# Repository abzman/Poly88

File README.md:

# Poly88
information related to the Poly88 s100 computer I've been repairing

This repository contains information other than boards, for those I've got a more generic set of S100 repro PCBs that for now mostly contains poly88 stuff: https://github.com/abzman/s100-PCBs

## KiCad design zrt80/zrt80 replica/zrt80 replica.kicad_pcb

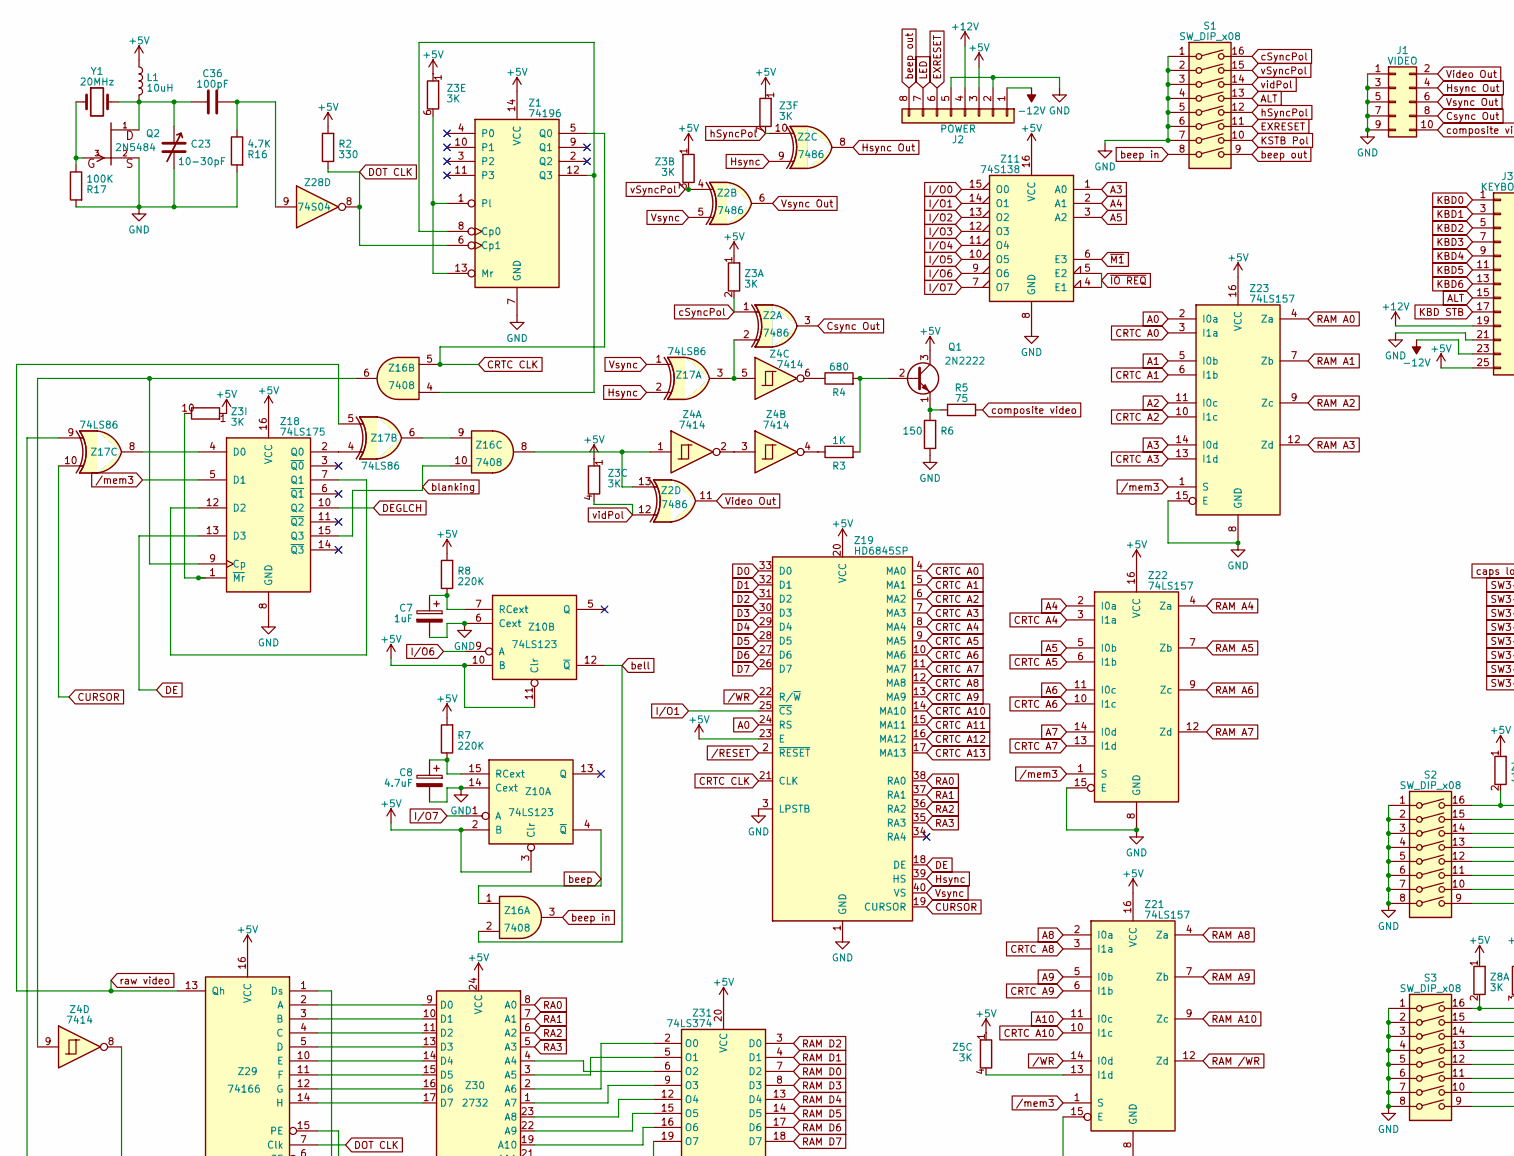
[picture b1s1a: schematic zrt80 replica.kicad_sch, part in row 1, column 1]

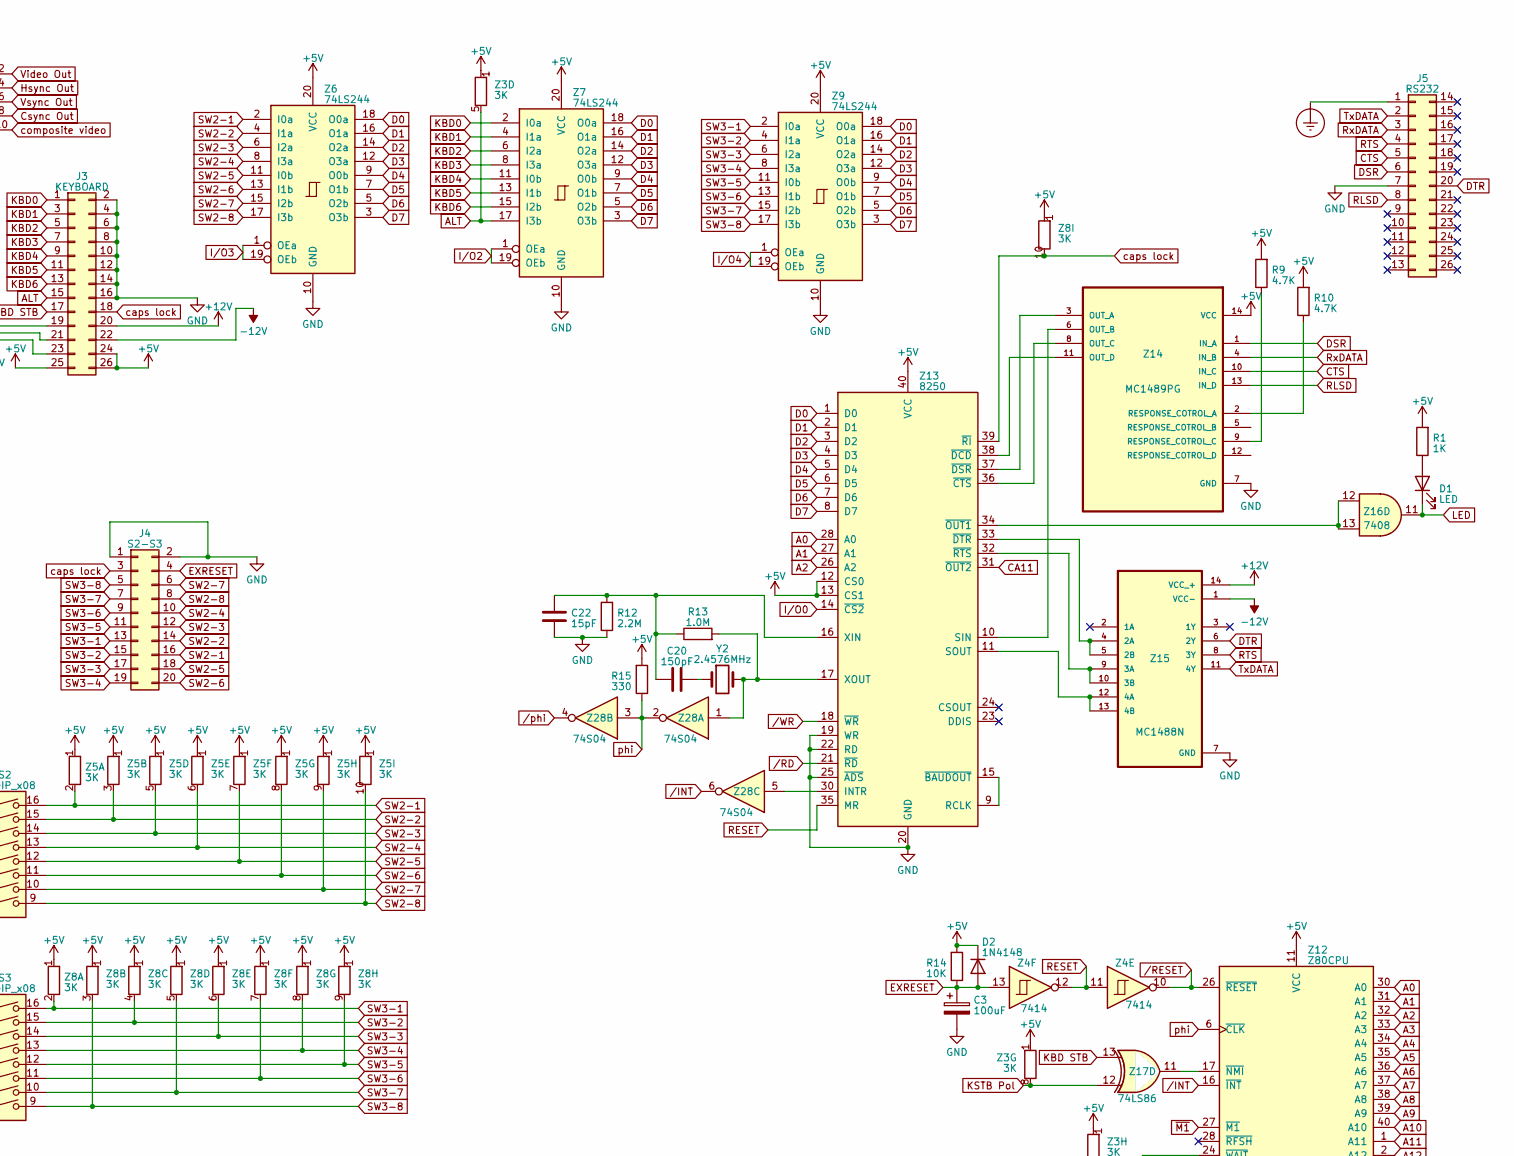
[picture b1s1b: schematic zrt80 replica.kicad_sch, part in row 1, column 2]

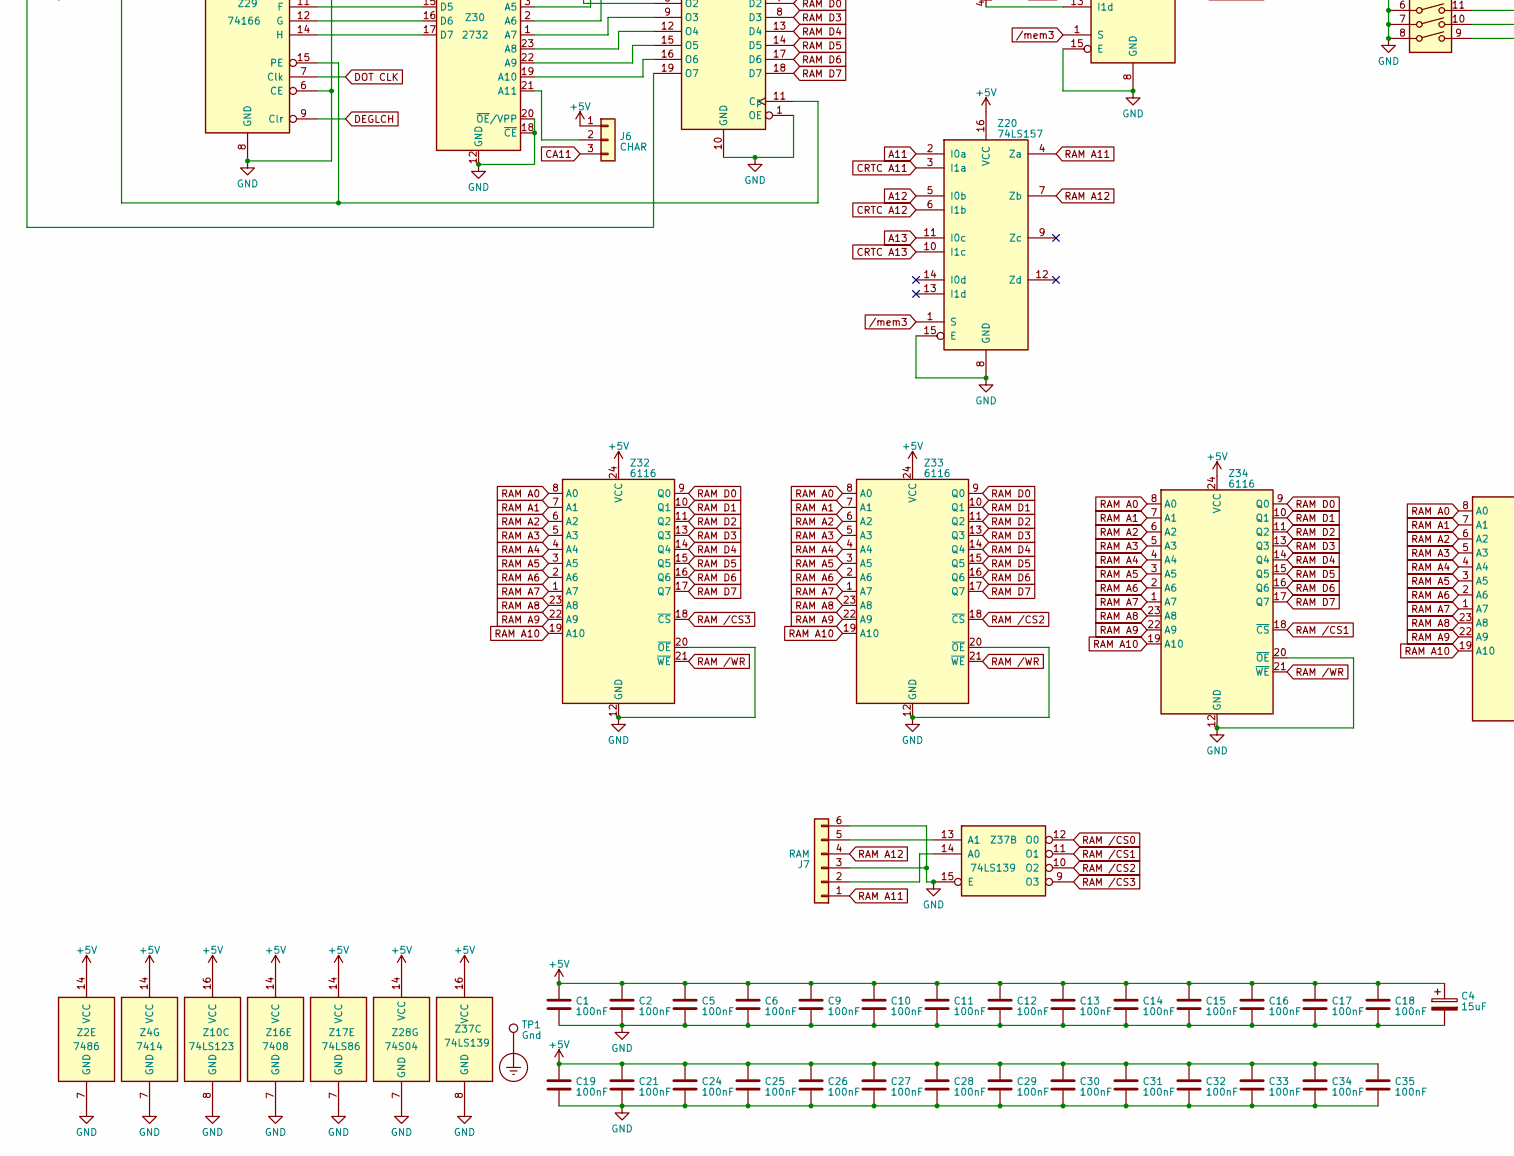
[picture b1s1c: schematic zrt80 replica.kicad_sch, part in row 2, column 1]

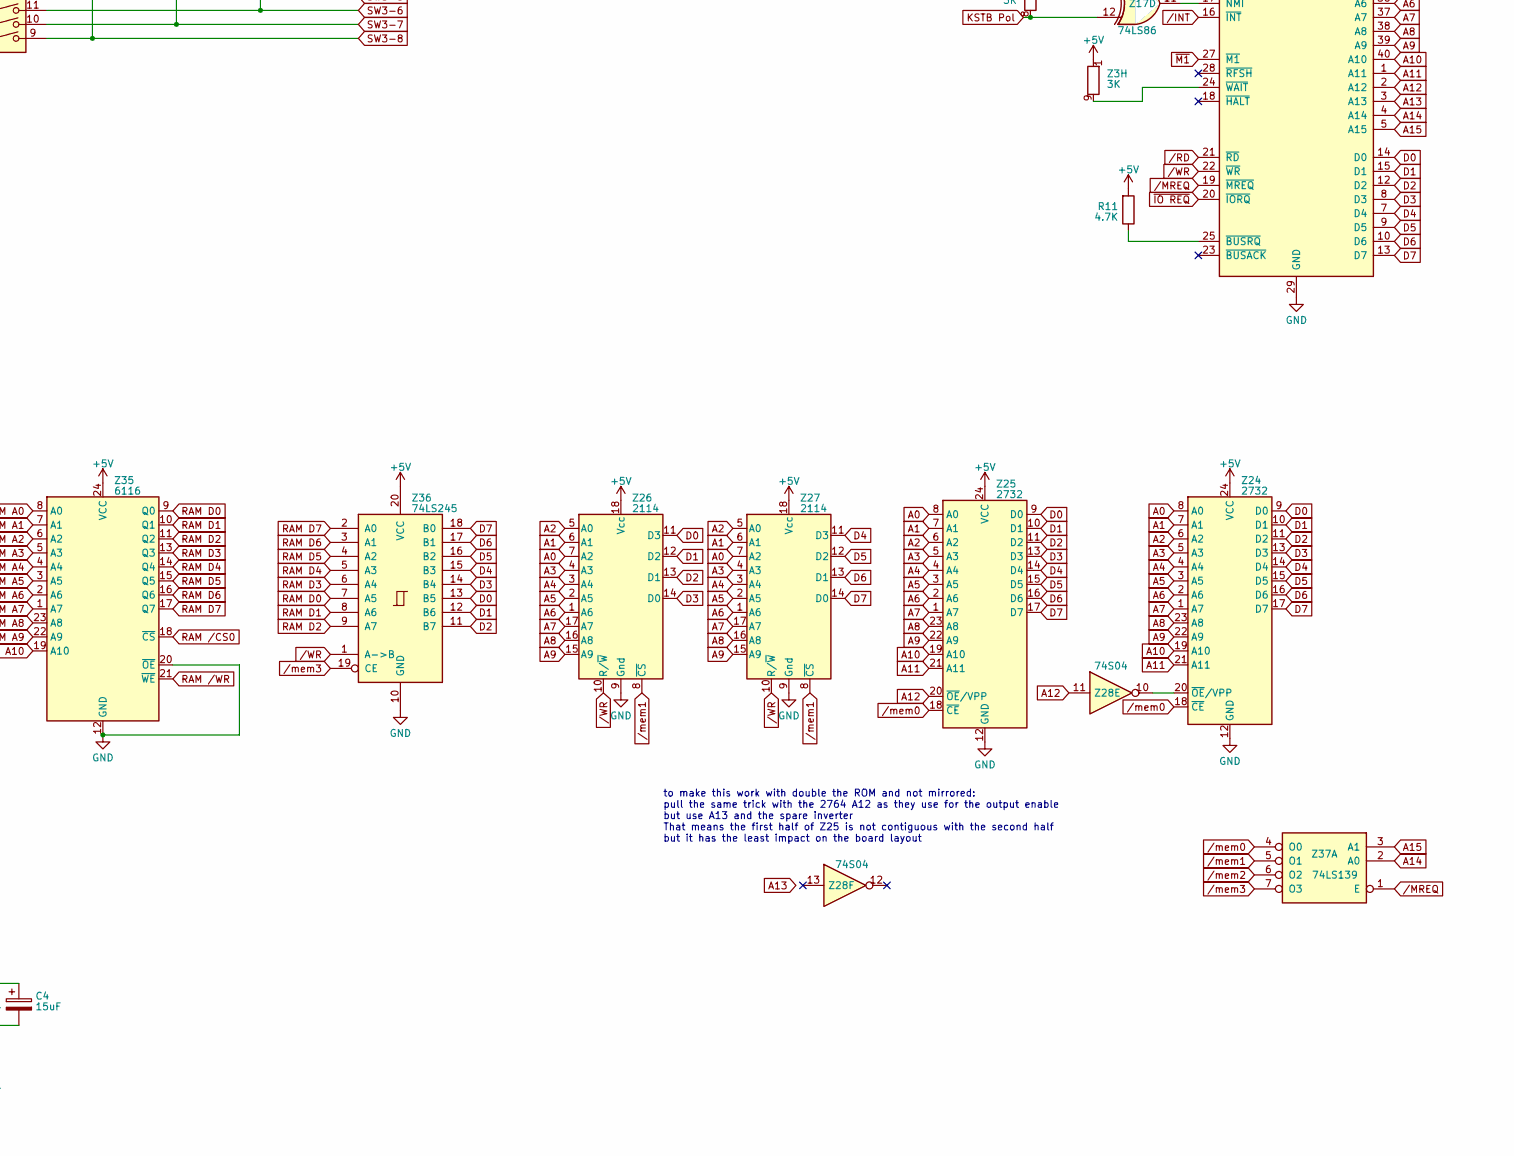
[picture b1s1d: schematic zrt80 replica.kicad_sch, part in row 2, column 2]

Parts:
C1, C2, C5, C6, C9, C10, C11, C12, C13, C14, C15, C16, C17, C18, C19, C21, C24, C25, C26, C27, C28, C29, C30, C31, C32, C33, C34, C35: 100nF; C_Disc_D6.0mm_W2.5mm_P6.35mm
C3: 100uF; CP_Radial_D10.0mm_P5.00mm
C4: 15uF; C_Disc_D6.0mm_W2.5mm_P6.35mm
C7: 1uF; C_Disc_D4.3mm_W1.9mm_P5.00mm
C8: 4.7uF; C_Disc_D4.3mm_W1.9mm_P5.00mm
C20: 150pF; C_Disc_D6.0mm_W2.5mm_P6.35mm
C22: 15pF; C_Disc_D6.0mm_W2.5mm_P6.35mm
C23: 10-30pF; trimmer cap
C36: 100pF; C_Disc_D6.0mm_W2.5mm_P6.35mm
D1: LED; LED_D5.0mm
D2: 1N4148; D_DO-35_SOD27_P12.70mm_Horizontal
J1: VIDEO; PinHeader_2x05_P2.54mm_Vertical
J2: POWER; TerminalBlock_Phoenix_MKDS-1,5-8-5.08_1x08_P5.08mm_Horizont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
J3: KEYBOARD; PinHeader_2x13_P2.54mm_Vertical
J4: S2-S3; PinHeader_2x10_P2.54mm_Vertical
J5: RS232; PinHeader_2x13_P2.54mm_Vertical
J6: CHAR; PinHeader_1x03_P2.54mm_Vertical
J7: RAM; PinHeader_1x06_P2.54mm_Vertical
L1: 10uH; L_Axial_L9.5mm_D4.0mm_P15.24mm_Horizontal_Fastron_SMCC
Q1: 2N2222; TO-5-3
Q2: 2N5484; TO-92L_Inline_Wide; PARTREV December, 2018
R1, R3: 1K; R_Axial_DIN0204_L3.6mm_D1.6mm_P12.7mm_Horizontal
R2, R15: 330; R_Axial_DIN0204_L3.6mm_D1.6mm_P12.7mm_Horizontal
R4: 680; R_Axial_DIN0204_L3.6mm_D1.6mm_P12.7mm_Horizontal
R5: 75; R_Axial_DIN0204_L3.6mm_D1.6mm_P12.7mm_Horizontal
R6: 150; R_Axial_DIN0204_L3.6mm_D1.6mm_P12.7mm_Horizontal
R7, R8: 220K; R_Axial_DIN0204_L3.6mm_D1.6mm_P12.7mm_Horizontal
R9, R10, R11, R16: 4.7K; R_Axial_DIN0204_L3.6mm_D1.6mm_P12.7mm_Horizontal
R12: 2.2M; R_Axial_DIN0204_L3.6mm_D1.6mm_P12.7mm_Horizontal
R13: 1.0M; R_Axial_DIN0204_L3.6mm_D1.6mm_P12.7mm_Horizontal
R14: 10K; R_Axial_DIN0204_L3.6mm_D1.6mm_P12.7mm_Horizontal
R17: 100K; R_Axial_DIN0204_L3.6mm_D1.6mm_P12.7mm_Horizontal
S1, S2, S3: SW_DIP_x08; SW_DIP_SPSTx08_Slide_6.7x21.88mm_W7.62mm_P2.54mm_LowProfile
TP1: Gnd; TestPoint_Plated_Hole_D2.0mm
Y1: 20MHz; Crystal_HC49-U_Vertical
Y2: 2.4576MHz; Crystal_HC33-U_Vertical
Z1: 74196; DIP-14_W7.62mm
Z2: 7486; DIP-14_W7.62mm
Z3, Z5, Z8: 3K; R_Array_SIP10
Z4: 7414; DIP-14_W7.62mm
Z6, Z7, Z9: 74LS244; DIP-20_W7.62mm
Z10: 74LS123; DIP-16_W7.62mm
Z11: 74S138; DIP-16_W7.62mm
Z12: Z80CPU; DIP-40_W15.24mm
Z13: 8250; DIP-40_W15.24mm
Z14: MC1489PG; DIP-14_W7.62mm; MPN MC1489PG
Z15: MC1488N; DIP-14_W7.62mm
Z16: 7408; DIP-14_W7.62mm
Z17: 74LS86; DIP-14_W7.62mm
Z18: 74LS175; DIP-16_W7.62mm
Z19: HD6845SP; DIP-40_W15.24mm
Z20, Z21, Z22, Z23: 74LS157; DIP-16_W7.62mm
Z24, Z25, Z30: 2732; DIP-24_W15.24mm
Z26, Z27: 2114; DIP-18_W7.62mm
Z28: 74S04; DIP-14_W7.62mm
Z29: 74166; DIP-16_W7.62mm
Z31: 74LS374; DIP-20_W7.62mm
Z32, Z33, Z34, Z35: 6116; DIP-24_W15.24mm
Z36: 74LS245; DIP-20_W7.62mm
Z37: 74LS139; DIP-16_W7.62mm

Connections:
+5V: C1.1, C2.1, C4.1, C5.1, C6.1, C9.1, C10.1, C11.1, C12.1, C13.1, C14.1, C15.1, C16.1, C17.1, C18.1, C19.1, C21.1, C24.1, C25.1, C26.1, C27.1, C28.1, C29.1, C30.1, C31.1, C32.1, C33.1, C34.1, C35.1, D2.1 (K), J2.3, J3.24, J3.25, J3.26, J6.1, L1.1, Q1.3 (C), R1.2, R2.2, R7.2, R8.2, R9.2, R10.2, R11.2, R14.2, R15.2, Z1.14 (VCC), Z2.14 (VCC), Z3.1 (R1.1), Z4.14 (VCC), Z5.1 (R1.1), Z6.20 (VCC), Z7.20 (VCC), Z8.1 (R1.1), Z9.20 (VCC), Z10.2 (B), Z10.3 (Clr), Z10.10 (B), Z10.11 (Clr), Z10.16 (VCC), Z11.16 (VCC), Z12.11 (VCC), Z13.12 (CS0), Z13.13 (CS1), Z13.40 (VCC), Z14.14 (VCC), Z16.14 (VCC), Z17.14 (VCC), Z18.16 (VCC), Z19.20 (VCC), Z19.23 (E), Z20.16 (VCC), Z21.16 (VCC), Z22.16 (VCC), Z23.16 (VCC), Z24.24 (VCC), Z25.24 (VCC), Z26.18 (Vcc), Z27.18 (Vcc), Z28.14 (VCC), Z29.16 (VCC), Z30.24 (VCC), Z31.20 (VCC), Z32.24 (VCC), Z33.24 (VCC), Z34.24 (VCC), Z35.24 (VCC), Z36.20 (VCC), Z37.16 (VCC)
+12V: J2.4, J3.19, J3.20, Z15.14 (VCC_+)
-12V: J2.1, J3.22, J3.23, Z15.1 (VCC-)
A0: Z12.30 (A0), Z13.28 (A0), Z19.24 (RS), Z23.2 (I0a), Z24.8 (A0), Z25.8 (A0), Z26.7 (A2), Z27.7 (A2)
A1: Z12.31 (A1), Z13.27 (A1), Z23.5 (I0b), Z24.7 (A1), Z25.7 (A1), Z26.6 (A1), Z27.6 (A1)
A2: Z12.32 (A2), Z13.26 (A2), Z23.11 (I0c), Z24.6 (A2), Z25.6 (A2), Z26.5 (A0), Z27.5 (A0)
A3: Z11.1 (A0), Z12.33 (A3), Z23.14 (I0d), Z24.5 (A3), Z25.5 (A3), Z26.4 (A3), Z27.4 (A3)
A4: Z11.2 (A1), Z12.34 (A4), Z22.2 (I0a), Z24.4 (A4), Z25.4 (A4), Z26.3 (A4), Z27.3 (A4)
A5: Z11.3 (A2), Z12.35 (A5), Z22.5 (I0b), Z24.3 (A5), Z25.3 (A5), Z26.2 (A5), Z27.2 (A5)
A6: Z12.36 (A6), Z22.11 (I0c), Z24.2 (A6), Z25.2 (A6), Z26.1 (A6), Z27.1 (A6)
A7: Z12.37 (A7), Z22.14 (I0d), Z24.1 (A7), Z25.1 (A7), Z26.17 (A7), Z27.17 (A7)
A8: Z12.38 (A8), Z21.2 (I0a), Z24.23 (A8), Z25.23 (A8), Z26.16 (A8), Z27.16 (A8)
A9: Z12.39 (A9), Z21.5 (I0b), Z24.22 (A9), Z25.22 (A9), Z26.15 (A9), Z27.15 (A9)
A10: Z12.40 (A10), Z21.11 (I0c), Z24.19 (A10), Z25.19 (A10)
A11: Z12.1 (A11), Z20.2 (I0a), Z24.21 (A11), Z25.21 (A11)
A12: Z12.2 (A12), Z20.5 (I0b), Z25.20 (~OE/VPP), Z28.11
A13: Z12.3 (A13), Z20.11 (I0c)
A14: Z12.4 (A14), Z37.2 (A0)
A15: Z12.5 (A15), Z37.3 (A1)
ALT: J3.15, S1.13, Z3.5 (R4.2), Z7.17 (I3b)
CA11: J6.3, Z13.31 (~OUT2)
CRTC A0: Z19.4 (MA0), Z23.3 (I1a)
CRTC A1: Z19.5 (MA1), Z23.6 (I1b)
CRTC A2: Z19.6 (MA2), Z23.10 (I1c)
CRTC A3: Z19.7 (MA3), Z23.13 (I1d)
CRTC A4: Z19.8 (MA4), Z22.3 (I1a)
CRTC A5: Z19.9 (MA5), Z22.6 (I1b)
CRTC A6: Z19.10 (MA6), Z22.10 (I1c)
CRTC A7: Z19.11 (MA7), Z22.13 (I1d)
CRTC A8: Z19.12 (MA8), Z21.3 (I1a)
CRTC A9: Z19.13 (MA9), Z21.6 (I1b)
CRTC A10: Z19.14 (MA10), Z21.10 (I1c)
CRTC A11: Z19.15 (MA11), Z20.3 (I1a)
CRTC A12: Z19.16 (MA12), Z20.6 (I1b)
CRTC A13: Z19.17 (MA13), Z20.10 (I1c)
CRTC CLK: Z1.5 (Q0), Z16.5, Z19.21 (CLK)
CTS: J5.5, Z14.10 (IN_C)
CURSOR: Z17.10, Z19.19 (CURSOR)
Csync Out: J1.8, Z2.3
D0: Z6.18 (O0a), Z7.18 (O0a), Z9.18 (O0a), Z12.14 (D0), Z13.1 (D0), Z19.33 (D0), Z24.9 (D0), Z25.9 (D0), Z26.11 (D3), Z36.13 (B5)
D1: Z6.16 (O1a), Z7.16 (O1a), Z9.16 (O1a), Z12.15 (D1), Z13.2 (D1), Z19.32 (D1), Z24.10 (D1), Z25.10 (D1), Z26.12 (D2), Z36.12 (B6)
D2: Z6.14 (O2a), Z7.14 (O2a), Z9.14 (O2a), Z12.12 (D2), Z13.3 (D2), Z19.31 (D2), Z24.11 (D2), Z25.11 (D2), Z26.13 (D1), Z36.11 (B7)
D3: Z6.12 (O3a), Z7.12 (O3a), Z9.12 (O3a), Z12.8 (D3), Z13.4 (D3), Z19.30 (D3), Z24.13 (D3), Z25.13 (D3), Z26.14 (D0), Z36.14 (B4)
D4: Z6.9 (O0b), Z7.9 (O0b), Z9.9 (O0b), Z12.7 (D4), Z13.5 (D4), Z19.29 (D4), Z24.14 (D4), Z25.14 (D4), Z27.11 (D3), Z36.15 (B3)
D5: Z6.7 (O1b), Z7.7 (O1b), Z9.7 (O1b), Z12.9 (D5), Z13.6 (D5), Z19.28 (D5), Z24.15 (D5), Z25.15 (D5), Z27.12 (D2), Z36.16 (B2)
D6: Z6.5 (O2b), Z7.5 (O2b), Z9.5 (O2b), Z12.10 (D6), Z13.7 (D6), Z19.27 (D6), Z24.16 (D6), Z25.16 (D6), Z27.13 (D1), Z36.17 (B1)
D7: Z6.3 (O3b), Z7.3 (O3b), Z9.3 (O3b), Z12.13 (D7), Z13.8 (D7), Z19.26 (D7), Z24.17 (D7), Z25.17 (D7), Z27.14 (D0), Z36.18 (B0)
DE: Z18.13 (D3), Z19.18 (DE)
DEGLCH: Z18.10 (Q2), Z29.9 (Clr)
DOT CLK: R2.1, Z1.6 (Cp1), Z28.8, Z29.7 (Clk)
DSR: J5.6, Z14.1 (IN_A)
DTR: J5.20, Z15.6 (2Y)
EXRESET: C3.1, D2.2 (A), J2.6, J4.4, R14.1, S1.11, Z4.13
Earth_Protective: J5.1, TP1.1
GND: C1.2, C2.2, C3.2, C4.2, C5.2, C6.2, C7.2, C8.2, C9.2, C10.2, C11.2, C12.2, C13.2, C14.2, C15.2, C16.2, C17.2, C18.2, C19.2, C21.2, C22.2, C23.2, C24.2, C25.2, C26.2, C27.2, C28.2, C29.2, C30.2, C31.2, C32.2, C33.2, C34.2, C35.2, J1.1, J1.3, J1.5, J1.7, J1.9, J2.2, J2.5, J3.2, J3.4, J3.6, J3.8, J3.10, J3.12, J3.14, J3.16, J3.21, J4.1, J4.2, J5.7, J7.3, J7.6, Q2.2, R6.1, R12.1, R16.2, R17.2, S1.1, S1.2, S1.3, S1.4, S1.5, S1.6, S1.7, S2.1, S2.2, S2.3, S2.4, S2.5, S2.6, S2.7, S2.8, S3.1, S3.2, S3.3, S3.4, S3.5, S3.6, S3.7, S3.8, Z1.7 (GND), Z2.7 (GND), Z4.7 (GND), Z6.10 (GND), Z7.10 (GND), Z9.10 (GND), Z10.6 (Cext), Z10.8 (GND), Z10.14 (Cext), Z11.8 (GND), Z12.29 (GND), Z13.19 (WR), Z13.20 (GND), Z13.22 (RD), Z13.25 (~ADS), Z14.7 (GND), Z15.7 (GND), Z16.7 (GND), Z17.7 (GND), Z18.8 (GND), Z19.1 (GND), Z19.3 (LPSTB), Z20.8 (GND), Z20.15 (E), Z21.8 (GND), Z21.15 (E), Z22.8 (GND), Z22.15 (E), Z23.8 (GND), Z23.15 (E), Z24.12 (GND), Z25.12 (GND), Z26.9 (Gnd), Z27.9 (Gnd), Z28.7 (GND), Z29.1 (Ds), Z29.6 (CE), Z29.8 (GND), Z30.12 (GND), Z30.18 (~CE), Z30.20 (~OE/VPP), Z31.1 (OE), Z31.10 (GND), Z32.12 (GND), Z32.20 (~OE), Z33.12 (GND), Z33.20 (~OE), Z34.12 (GND), Z34.20 (~OE), Z35.12 (GND), Z35.20 (~OE), Z36.10 (GND), Z37.8 (GND), Z37.15 (E)
Hsync: Z2.9, Z17.2, Z19.39 (HS)
Hsync Out: J1.4, Z2.8
I/O0: Z11.15 (O0), Z13.14 (~CS2)
I/O1: Z11.14 (O1), Z19.25 (~CS)
I/O2: Z7.1 (OEa), Z7.19 (OEb), Z11.13 (O2)
I/O3: Z6.1 (OEa), Z6.19 (OEb), Z11.12 (O3)
I/O4: Z9.1 (OEa), Z9.19 (OEb), Z11.11 (O4)
I/O5: Z11.10 (O5)
I/O6: Z10.9 (A), Z11.9 (O6)
I/O7: Z10.1 (A), Z11.7 (O7)
KBD0: J3.1, Z7.2 (I0a)
KBD1: J3.3, Z7.4 (I1a)
KBD2: J3.5, Z7.6 (I2a)
KBD3: J3.7, Z7.8 (I3a)
KBD4: J3.9, Z7.11 (I0b)
KBD5: J3.11, Z7.13 (I1b)
KBD6: J3.13, Z7.15 (I2b)
KBD STB: J3.17, Z17.13
KSTB Pol: S1.10, Z3.8 (R7.2), Z17.12
LED: D1.1 (K), J2.7, Z16.11
unnamed: C20.2, Y2.1
unnamed: C23.1, C36.1, L1.2, Q2.1, Y1.2
unnamed: C36.2, R16.1, Z28.9
unnamed: D1.2 (A), R1.1
unnamed: J6.2, Z30.21 (A11)
unnamed: J7.2, Z37.14 (A0)
unnamed: J7.5, Z37.13 (A1)
unnamed: Q1.2 (B), R3.2, R4.2
unnamed: Q1.1 (E), R5.1, R6.2
unnamed: Q2.3, R17.1, Y1.1
unnamed: R3.1, Z4.4
unnamed: R4.1, Z4.6
unnamed: Z1.8 (Cp0), Z1.12 (Q3), Z16.4
unnamed: Z1.1 (Pl), Z1.13 (Mr), Z3.6 (R5.2)
unnamed: Z4.2, Z4.3
unnamed: C8.1, R7.1, Z10.15 (RCext)
unnamed: C7.1, R8.1, Z10.7 (RCext)
unnamed: R11.1, Z12.25 (~BUSRQ)
unnamed: Z12.17 (~NMI), Z17.11
unnamed: Z3.9 (R8.2), Z12.24 (~WAIT)
unnamed: Z13.30 (INTR), Z28.5
unnamed: Z13.9 (RCLK), Z13.15 (~BAUDOUT)
unnamed: Z13.10 (SIN), Z14.6 (OUT_B)
unnamed: Z13.11 (SOUT), Z15.12 (4A), Z15.13 (4B)
unnamed: C20.1, C22.1, R12.2, R13.1, Z13.16 (XIN)
unnamed: R13.2, Y2.2, Z13.17 (XOUT), Z28.1
unnamed: Z13.36 (~CTS), Z14.8 (OUT_C)
unnamed: Z13.38 (~DCD), Z14.11 (OUT_D)
unnamed: Z13.37 (~DSR), Z14.3 (OUT_A)
unnamed: Z13.33 (~DTR), Z15.4 (2A), Z15.5 (2B)
unnamed: Z13.34 (~OUT1), Z16.12, Z16.13
unnamed: Z13.32 (~RTS), Z15.9 (3A), Z15.10 (3B)
unnamed: R10.1, Z14.2 (RESPONSE_COTROL_A)
unnamed: R9.1, Z14.9 (RESPONSE_COTROL_C)
unnamed: Z2.13, Z4.1, Z16.8
unnamed: Z16.9, Z17.6
unnamed: Z2.2, Z4.5, Z17.3
unnamed: Z4.9, Z16.6, Z18.9 (Cp)
unnamed: Z17.8, Z18.4 (D0)
unnamed: Z18.7 (Q1), Z18.12 (D2)
unnamed: Z17.4, Z18.2 (Q0)
unnamed: Z3.10 (R9.2), Z18.1 (~Mr)
unnamed: Z5.4 (R3.2), Z21.13 (I1d)
unnamed: Z24.20 (~OE/VPP), Z28.10
unnamed: Z29.2 (A), Z30.9 (D0)
unnamed: Z29.3 (B), Z30.10 (D1)
unnamed: Z29.4 (C), Z30.11 (D2)
unnamed: Z29.5 (D), Z30.13 (D3)
unnamed: Z29.10 (E), Z30.14 (D4)
unnamed: Z29.11 (F), Z30.15 (D5)
unnamed: Z29.12 (G), Z30.16 (D6)
unnamed: Z29.14 (H), Z30.17 (D7)
unnamed: Z4.8, Z29.15 (PE), Z31.11 (Cp)
unnamed: Z30.4 (A4), Z31.6 (O2)
unnamed: Z30.3 (A5), Z31.5 (O1)
unnamed: Z30.2 (A6), Z31.2 (O0)
unnamed: Z30.1 (A7), Z31.9 (O3)
unnamed: Z30.23 (A8), Z31.12 (O4)
unnamed: Z30.22 (A9), Z31.15 (O5)
unnamed: Z30.19 (A10), Z31.16 (O6)
unnamed: Z17.9, Z31.19 (O7)
RA0: Z19.38 (RA0), Z30.8 (A0)
RA1: Z19.37 (RA1), Z30.7 (A1)
RA2: Z19.36 (RA2), Z30.6 (A2)
RA3: Z19.35 (RA3), Z30.5 (A3)
RAM A0: Z23.4 (Za), Z32.8 (A0), Z33.8 (A0), Z34.8 (A0), Z35.8 (A0)
RAM A1: Z23.7 (Zb), Z32.7 (A1), Z33.7 (A1), Z34.7 (A1), Z35.7 (A1)
RAM A2: Z23.9 (Zc), Z32.6 (A2), Z33.6 (A2), Z34.6 (A2), Z35.6 (A2)
RAM A3: Z23.12 (Zd), Z32.5 (A3), Z33.5 (A3), Z34.5 (A3), Z35.5 (A3)
RAM A4: Z22.4 (Za), Z32.4 (A4), Z33.4 (A4), Z34.4 (A4), Z35.4 (A4)
RAM A5: Z22.7 (Zb), Z32.3 (A5), Z33.3 (A5), Z34.3 (A5), Z35.3 (A5)
RAM A6: Z22.9 (Zc), Z32.2 (A6), Z33.2 (A6), Z34.2 (A6), Z35.2 (A6)
RAM A7: Z22.12 (Zd), Z32.1 (A7), Z33.1 (A7), Z34.1 (A7), Z35.1 (A7)
RAM A8: Z21.4 (Za), Z32.23 (A8), Z33.23 (A8), Z34.23 (A8), Z35.23 (A8)
RAM A9: Z21.7 (Zb), Z32.22 (A9), Z33.22 (A9), Z34.22 (A9), Z35.22 (A9)
RAM A10: Z21.9 (Zc), Z32.19 (A10), Z33.19 (A10), Z34.19 (A10), Z35.19 (A10)
RAM A11: J7.1, Z20.4 (Za)
RAM A12: J7.4, Z20.7 (Zb)
RAM D0: Z31.7 (D2), Z32.9 (Q0), Z33.9 (Q0), Z34.9 (Q0), Z35.9 (Q0), Z36.7 (A5)
RAM D1: Z31.4 (D1), Z32.10 (Q1), Z33.10 (Q1), Z34.10 (Q1), Z35.10 (Q1), Z36.8 (A6)
RAM D2: Z31.3 (D0), Z32.11 (Q2), Z33.11 (Q2), Z34.11 (Q2), Z35.11 (Q2), Z36.9 (A7)
RAM D3: Z31.8 (D3), Z32.13 (Q3), Z33.13 (Q3), Z34.13 (Q3), Z35.13 (Q3), Z36.6 (A4)
RAM D4: Z31.13 (D4), Z32.14 (Q4), Z33.14 (Q4), Z34.14 (Q4), Z35.14 (Q4), Z36.5 (A3)
RAM D5: Z31.14 (D5), Z32.15 (Q5), Z33.15 (Q5), Z34.15 (Q5), Z35.15 (Q5), Z36.4 (A2)
RAM D6: Z31.17 (D6), Z32.16 (Q6), Z33.16 (Q6), Z34.16 (Q6), Z35.16 (Q6), Z36.3 (A1)
RAM D7: Z31.18 (D7), Z32.17 (Q7), Z33.17 (Q7), Z34.17 (Q7), Z35.17 (Q7), Z36.2 (A0)
RAM /CS0: Z35.18 (~CS), Z37.12 (O0)
RAM /CS1: Z34.18 (~CS), Z37.11 (O1)
RAM /CS2: Z33.18 (~CS), Z37.10 (O2)
RAM /CS3: Z32.18 (~CS), Z37.9 (O3)
RAM /WR: Z21.12 (Zd), Z32.21 (~WE), Z33.21 (~WE), Z34.21 (~WE), Z35.21 (~WE)
RESET: Z4.11, Z4.12, Z13.35 (MR)
RLSD: J5.8, Z14.13 (IN_D)
RTS: J5.4, Z15.8 (3Y)
RxDATA: J5.3, Z14.4 (IN_B)
SW2-1: J4.16, S2.16, Z5.2 (R1.2), Z6.2 (I0a)
SW2-2: J4.14, S2.15, Z5.3 (R2.2), Z6.4 (I1a)
SW2-3: J4.12, S2.14, Z5.5 (R4.2), Z6.6 (I2a)
SW2-4: J4.10, S2.13, Z5.6 (R5.2), Z6.8 (I3a)
SW2-5: J4.18, S2.12, Z5.7 (R6.2), Z6.11 (I0b)
SW2-6: J4.20, S2.11, Z5.8 (R7.2), Z6.13 (I1b)
SW2-7: J4.6, S2.10, Z5.9 (R8.2), Z6.15 (I2b)
SW2-8: J4.8, S2.9, Z5.10 (R9.2), Z6.17 (I3b)
SW3-1: J4.13, S3.16, Z8.2 (R1.2), Z9.2 (I0a)
SW3-2: J4.15, S3.15, Z8.4 (R3.2), Z9.4 (I1a)
SW3-3: J4.17, S3.14, Z8.6 (R5.2), Z9.6 (I2a)
SW3-4: J4.19, S3.13, Z8.8 (R7.2), Z9.8 (I3a)
SW3-5: J4.11, S3.12, Z8.9 (R8.2), Z9.11 (I0b)
SW3-6: J4.9, S3.11, Z8.7 (R6.2), Z9.13 (I1b)
SW3-7: J4.7, S3.10, Z8.5 (R4.2), Z9.15 (I2b)
SW3-8: J4.5, S3.9, Z8.3 (R2.2), Z9.17 (I3b)
TxDATA: J5.2, Z15.11 (4Y)
Video Out: J1.2, Z2.11
Vsync: Z2.5, Z17.1, Z19.40 (VS)
Vsync Out: J1.6, Z2.6
beep: Z10.4 (~Q), Z16.1
beep in: S1.8, Z16.3
beep out: J2.8, S1.9
bell: Z10.12 (~Q), Z16.2
blanking: Z16.10, Z18.15 (Q3)
cSyncPol: S1.16, Z2.1, Z3.2 (R1.2)
caps lock: J3.18, J4.3, Z8.10 (R9.2), Z13.39 (~RI)
composite video: J1.10, R5.2
hSyncPol: S1.12, Z2.10, Z3.7 (R6.2)
phi: R15.1, Z12.6 (~CLK), Z28.2, Z28.3
raw video: Z17.5, Z29.13 (Qh)
vSyncPol: S1.15, Z2.4, Z3.3 (R2.2)
vidPol: S1.14, Z2.12, Z3.4 (R3.2)
/INT: Z12.16 (~INT), Z28.6
/MREQ: Z12.19 (~MREQ), Z37.1 (E)
/RD: Z12.21 (~RD), Z13.21 (~RD)
/RESET: Z4.10, Z12.26 (~RESET), Z19.2 (~RESET)
/WR: Z12.22 (~WR), Z13.18 (~WR), Z19.22 (R/~W), Z21.14 (I0d), Z26.10 (R/~W), Z27.10 (R/~W), Z36.1 (A->B)
/mem0: Z24.18 (~CE), Z25.18 (~CE), Z37.4 (O0)
/mem1: Z26.8 (~CS), Z27.8 (~CS), Z37.5 (O1)
/mem2: Z37.6 (O2)
/mem3: Z18.5 (D1), Z20.1 (S), Z21.1 (S), Z22.1 (S), Z23.1 (S), Z36.19 (CE), Z37.7 (O3)
/phi: Z28.4
~IO REQ: Z11.4 (E1), Z11.5 (E2), Z12.20 (~IORQ)
~M1: Z11.6 (E3), Z12.27 (~M1)

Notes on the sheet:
to make this work with double the ROM and not mirrored: pull the same trick with the 2764 A12 as they use for the output enable but use A13 and the spare inverter That means the first half of Z25 is not contiguous with the second half but it has the least impact on the board layout

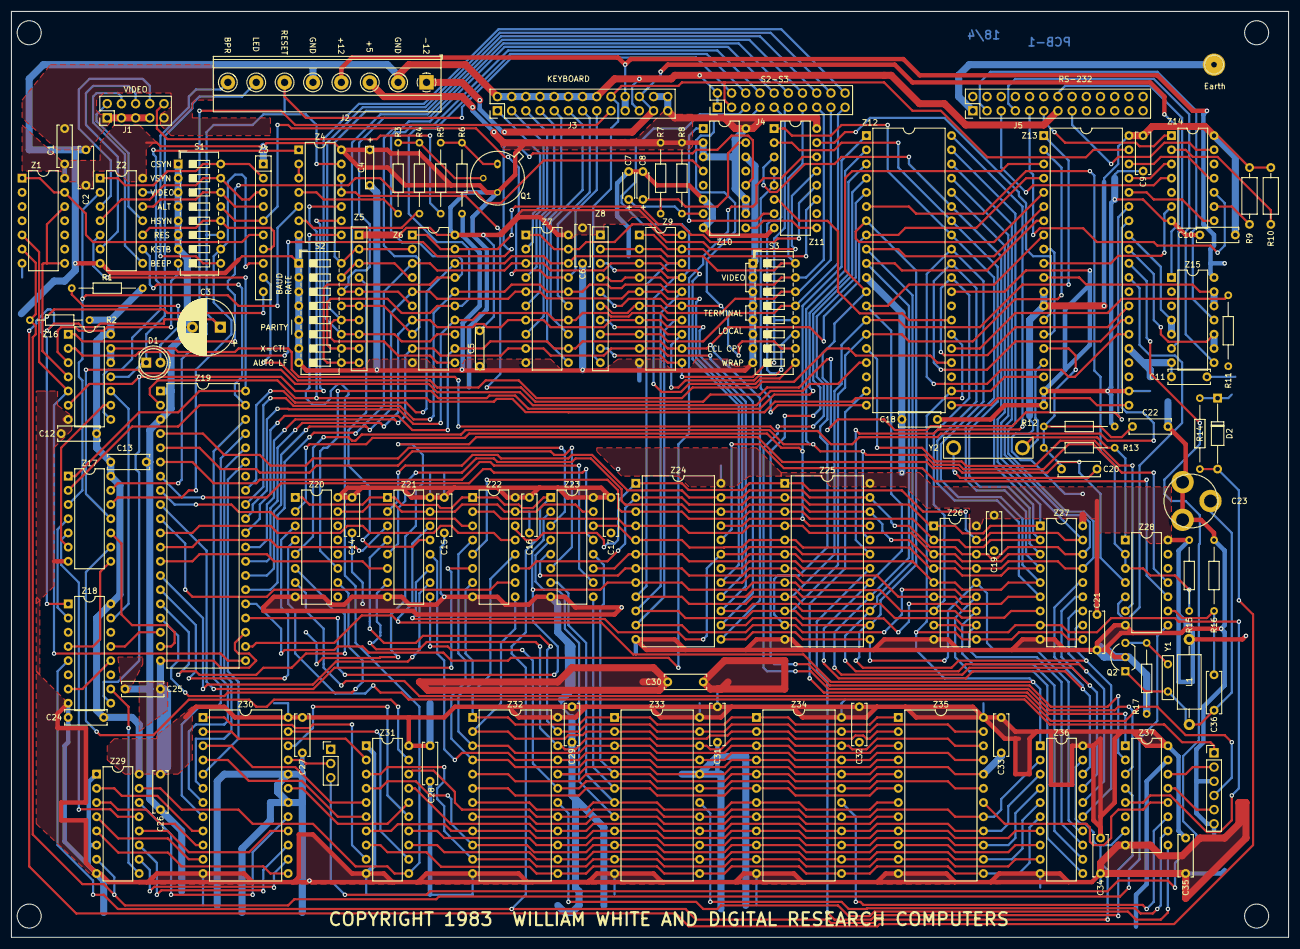
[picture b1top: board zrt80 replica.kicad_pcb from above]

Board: 2 copper layers, 228.6 x 165.7 mm, 108 parts (0 on the bottom side), 212 nets.

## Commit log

2020-10-25 zrt80 zip file added (contents)
2020-10-25 added files from Frank's github
2020-10-25 added byte font from the internet
2020-10-25 added Frank's disassembly
2020-10-25 added basic stuff
2023-06-09 added initial unfinished lid for 4 hole lid
2023-07-10 made changes from first revision
2023-08-03 tweaked cad based on feedback from someone with real lids
2024-02-21 added keyboard lid first pass
2024-02-27 added keyboard stabalizer parts
2024-03-28 picked parts, values, and red-des for zrt80 replica
2024-03-29 schematic 'done'
2024-04-01 layout for zrt80 progressing
2024-04-02 continued zrt80 layout
2024-04-03 finished initial layout of zrt-80
2024-04-03 updated silk and added note for doubling the rom
2024-04-19 added doubler files

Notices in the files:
zrt80/zrt80 replica/zrt80 replica.kicad_pcb:
COPYRIGHT 1983  WILLIAM WHITE AND DIGITAL RESEARCH COMPUTERS
